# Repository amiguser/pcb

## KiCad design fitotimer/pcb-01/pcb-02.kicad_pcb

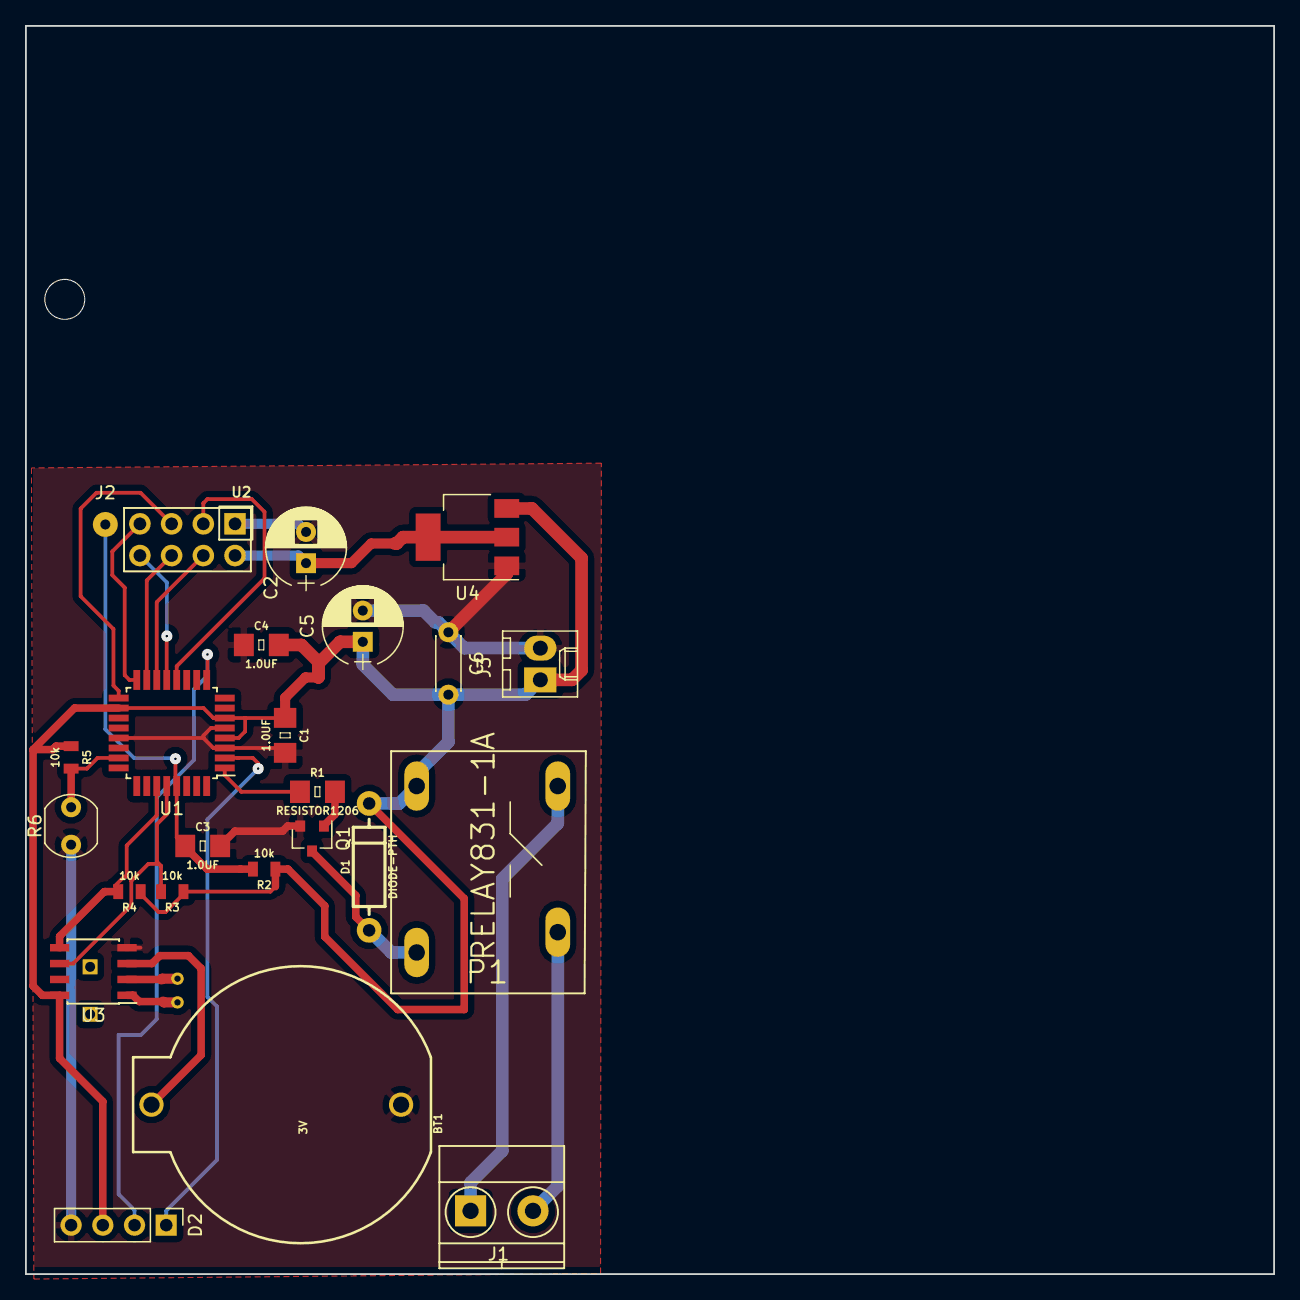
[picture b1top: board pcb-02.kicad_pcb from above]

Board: 2 copper layers, 100.0 x 100.0 mm, 25 parts (1 on the bottom side), 23 nets.

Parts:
BT1: 3V; BATTCOM_20MM_PTH
C1, C3, C4: 1.0UF; 1206
C2: 22mF; CP_Radial_D6.3mm_P2.50mm
C5: 470mF; CP_Radial_D6.3mm_P2.50mm
C6: 1.0UF; C_Disc_D4.3mm_W1.9mm_P5.00mm
D1: DIODE-PTH; DIODE-1N4001
D2: TM1637Module; Pin_Header_Straight_1x04_Pitch2.54mm
J1: Screw_Terminal_01x02; TerminalBlock_Pheonix_MKDS1.5-2pol
J2: CONN_01POGOPIN_HOLE_0.58; SolderWirePad_single_0-8mmDrill
J3: +5DC; Molex_KK-6410-02_02x2.54mm_Straight
P1: RELAY831-1A; Relay-841-1A
Q1: BC847; SOT-23
R1: RESISTOR1206; 1206
R2, R3, R4, R5: 10k; 0805
R6: A9013; Resistor_LDR_5x4.1_RM3
U1: ATMEGA8-16AU; TQFP-32_7x7mm_Pitch0.8mm
U2: NRF24L01
U3: DS1307Z; SOIC-8_3.9x4.9mm_Pitch1.27mm
U4: LM1117 3v3; SOT-223
Y1: 32768; Crystal_C38-LF_d3.0mm_l8.0mm_Horizontal_1EP_style2

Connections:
+5VD: C1.1, C4.2, C5.1, C6.2, D1.C, D2.3, J3.1, P1.1, R2.1, R3.1, R4.1, R5.1, U1.4, U1.6, U1.18, U3.8, U4.3
ADC0: R5.2, R6.2, U1.23
GND: BT1.2, C1.2, C2.2, C3.2, C4.1, C5.2, C6.1, D2.4, J3.2, Q1.2, R6.1, U1.3, U1.5, U1.21, U2.1, U3.4, U4.1
MISO: U1.16, U2.7
MOSI: U1.15, U2.6
unnamed: BT1.1, U3.3
unnamed: C2.1, U2.2, U4.2, U4.4
unnamed: D1.A, P1.2, Q1.3
unnamed: J1.1, P1.3
unnamed: J1.2, P1.4
unnamed: Q1.1, R1.2
unnamed: U3.1, Y1.1
unnamed: U3.2, Y1.2
PB0: U1.12, U2.3
PB1: U1.13, U2.8
PB2: U1.14, U2.4
RESET: C3.1, J2.1, R2.2, U1.29
SCK: U1.17, U2.5
SCL: R3.2, U1.28, U3.6
SDA: R4.2, U1.27, U3.5
pd3: R1.1, U1.1
pd4: D2.1, U1.2
pd5: D2.2, U1.9

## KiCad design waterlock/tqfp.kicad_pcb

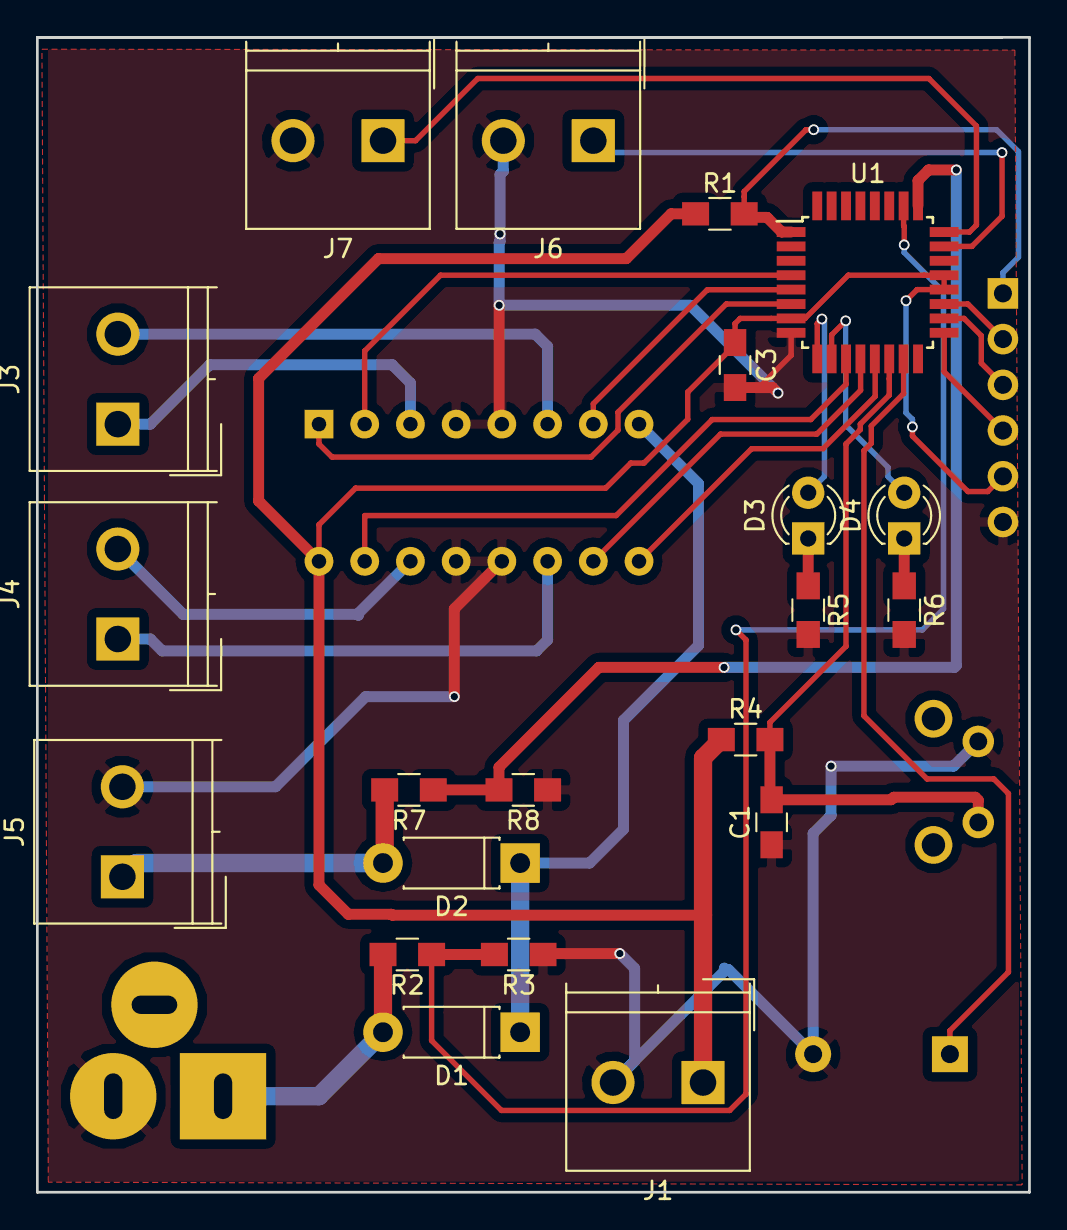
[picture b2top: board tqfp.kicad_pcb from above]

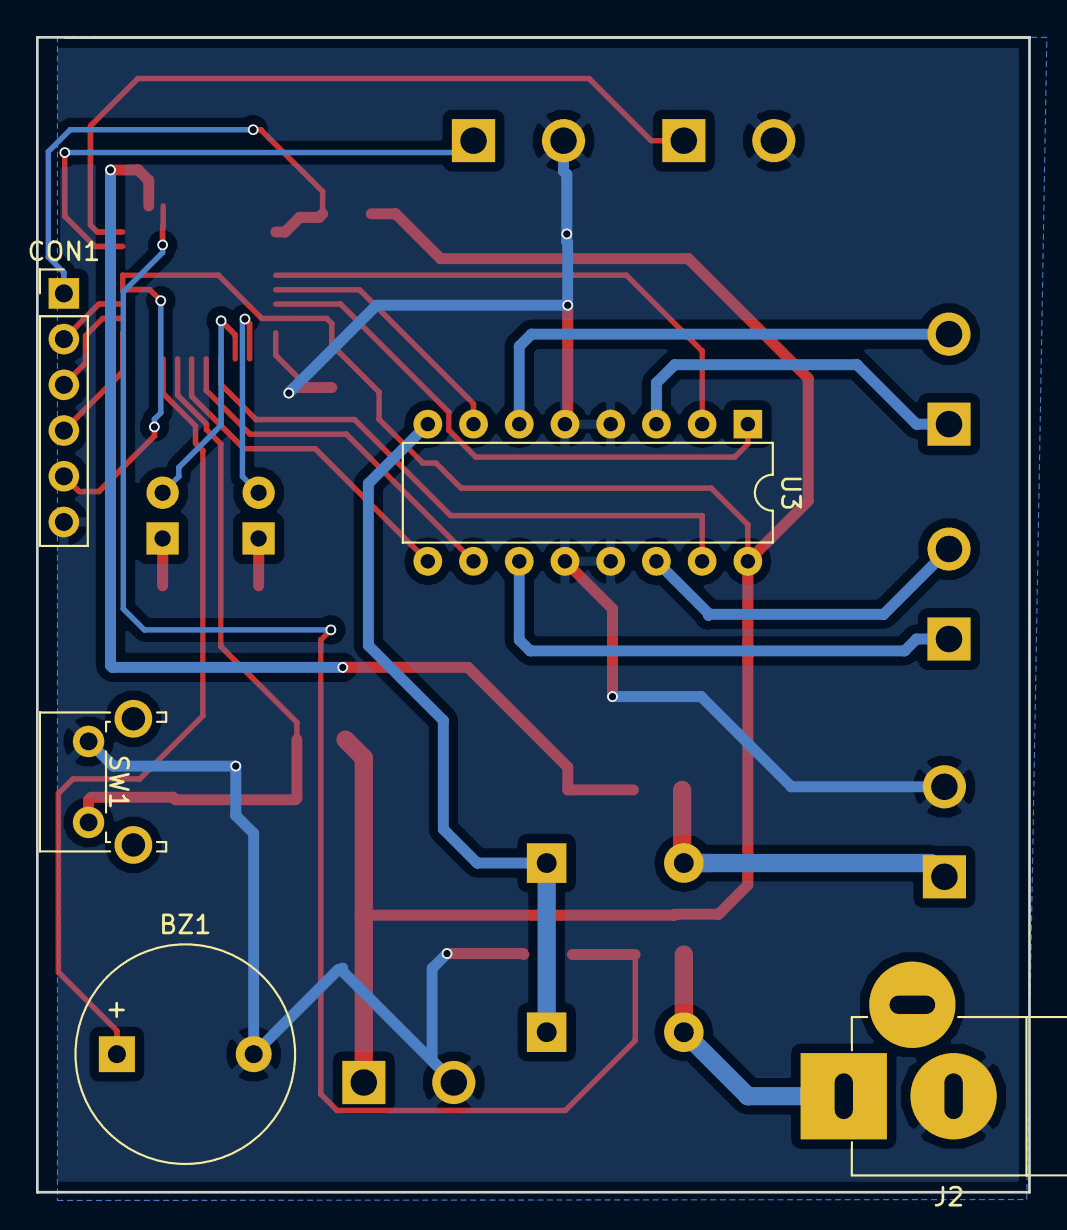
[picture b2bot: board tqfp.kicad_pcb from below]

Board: 2 copper layers, 55.1 x 64.2 mm, 26 parts (5 on the bottom side), 29 nets.

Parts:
BZ1: Buzzer; Buzzer_12x9.5RM7.6
C1, C3: 10m; C_0805_HandSoldering
CON1: AVR-ISP-10; Pin_Header_Straight_1x06_Pitch2.54mm
D1, D2: 1N; D_DO-41_SOD81_P7.62mm_Horizontal
D3: LowBatt; LED_D3.0mm
D4: Flooding; LED_D3.0mm
J1: v5; TerminalBlock_Philmore_TB132_02x5mm_Straight
J2: v12; JACK_ALIM
J3: m1; TerminalBlock_Philmore_TB132_02x5mm_Straight
J4: m2; TerminalBlock_Philmore_TB132_02x5mm_Straight
J5: Battery; TerminalBlock_Philmore_TB132_02x5mm_Straight
J6: L1; TerminalBlock_Philmore_TB132_02x5mm_Straight
J7: L2; TerminalBlock_Philmore_TB132_02x5mm_Straight
R1, R4, R5, R6: 10k; R_0805_HandSoldering
R2, R7: 47k; R_0805_HandSoldering
R3, R8: 68k; R_0805_HandSoldering
SW1: Turn; SW_Tactile_SPST_Angled_PTS645Vx58-2LFS
U1: ATMEGA8-16PU; TQFP-32_7x7mm_Pitch0.8mm
U3: L293D; DIP-16_W7.62mm

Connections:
+5V: C3.1, CON1.5, J1.1, R1.1, R4.1, U1.7, U1.20, U1.21, U3.16
+12V: D1.1, D2.1, U3.8
/Line1: J6.1, U1.23
/Line2: J7.1, U1.24
/MISO: CON1.3, U1.18
/MOSI: CON1.4, U1.17
/RESET: CON1.1, R1.2, U1.1
/SCK: CON1.2, U1.19
/acdc_pwr: D1.2, J2.1, R2.2
/btn_1: C1.2, R4.2, SW1.1, U1.14
/buzz: BZ1.1, U1.15
/en12: U1.6, U3.1
/en34: U1.13, U3.9
/led1: D3.2, U1.9
/led2: D4.2, U1.10
/m1a: U1.4, U3.2
/m2a: U1.5, U3.7
/m3a: U1.12, U3.10
/m4a: U1.11, U3.15
/pwr_c1: R7.1, R8.2, U1.25
/pwr_c2: R2.1, R3.2, U1.26
GND: BZ1.2, C1.1, C3.2, CON1.6, J1.2, J2.2, J5.2, J6.2, J7.2, R3.1, R5.2, R6.2, R8.1, SW1.2, U1.8, U1.22, U3.4, U3.5, U3.12, U3.13
unnamed: D2.2, J5.1, R7.2
unnamed: D3.1, R5.1
unnamed: D4.1, R6.1
unnamed: J3.1, U3.3
unnamed: J3.2, U3.6
unnamed: J4.1, U3.11
unnamed: J4.2, U3.14
